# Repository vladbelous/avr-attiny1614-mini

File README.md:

# AVR Attiny1614 (tinyAVR 1-Series) mini board

This is a simple breakout board for Attiny1614 MCU with a button and some pins dedicated to switching loads via MOSFETs.

Attiny1614 ([datasheet](http://ww1.microchip.com/downloads/en/DeviceDoc/ATtiny1614-data-sheet-40001995A.pdf)) is a new 8-bit AVR part from tinyAVR 1-Series.
In many important ways its architecture is much closer to atxmega rather than to (previous) attiny/atmega parts.
In fact, in avr-gcc it is categorized under avrxmega3 architecture.

This particular board has:
* Pin PA4 connected to high-side P-MOSFET for powering/driving an external component, using same VIN supply and common GND. This pin is **active low**.
* Pin PA5  connected to low-side N-MOSFET for driving a load using a separate supply (VEXT pin). Grounds levels will be separate. This pin is **active high**.
* Footprints for optional pull-up resistors for I2C.

This board has already been fabricated and tested to work.
It is available as a [shared project on OSHPark](https://oshpark.com/shared_projects/I7XN0JuT).

### Note on UPDI/~RESET pin:
Pin PA0 (UPDI/~RESET) can be used for either programming (via UPDI protocol) or RESET source functionality, but *you have to choose* between the two via a fuse setting. By default the fuse is setup for UPDI.

If you set the fuses for RESET source, programming the chip will require applying 12V, which is somewhat inconvenient.

Some workarounds:
* Keep the fuse in UPDI mode: you can still use the pin as digital input, and hence implement reset functionality in software (e.g. via interrupt, polling, etc). This is less reliable, since it assumes your MCU is in working state.
* Use/create a bootloader (I'm not aware of any existing yet for this part) that will allow you to program the chip via UART (similar to Arduino). Then you can change the fuse to enable it as RESET source.

Overall, this presents some inconvenience in scenarios when you need a reliable RESET.
This may be important in low voltage situations -- if your MCU gets stuck in some non-working state, a physical RESET signal is needed. Some mitigation is paying more attention to BOD (brown-out detection) settings.

### Development toolchain:
See https://github.com/vladbelous/tinyAVR_gcc_setup for details on how to setup a toolchain based on avr-gcc, avrdude and jtag2updi.

## Schematic:

## Layout (front):

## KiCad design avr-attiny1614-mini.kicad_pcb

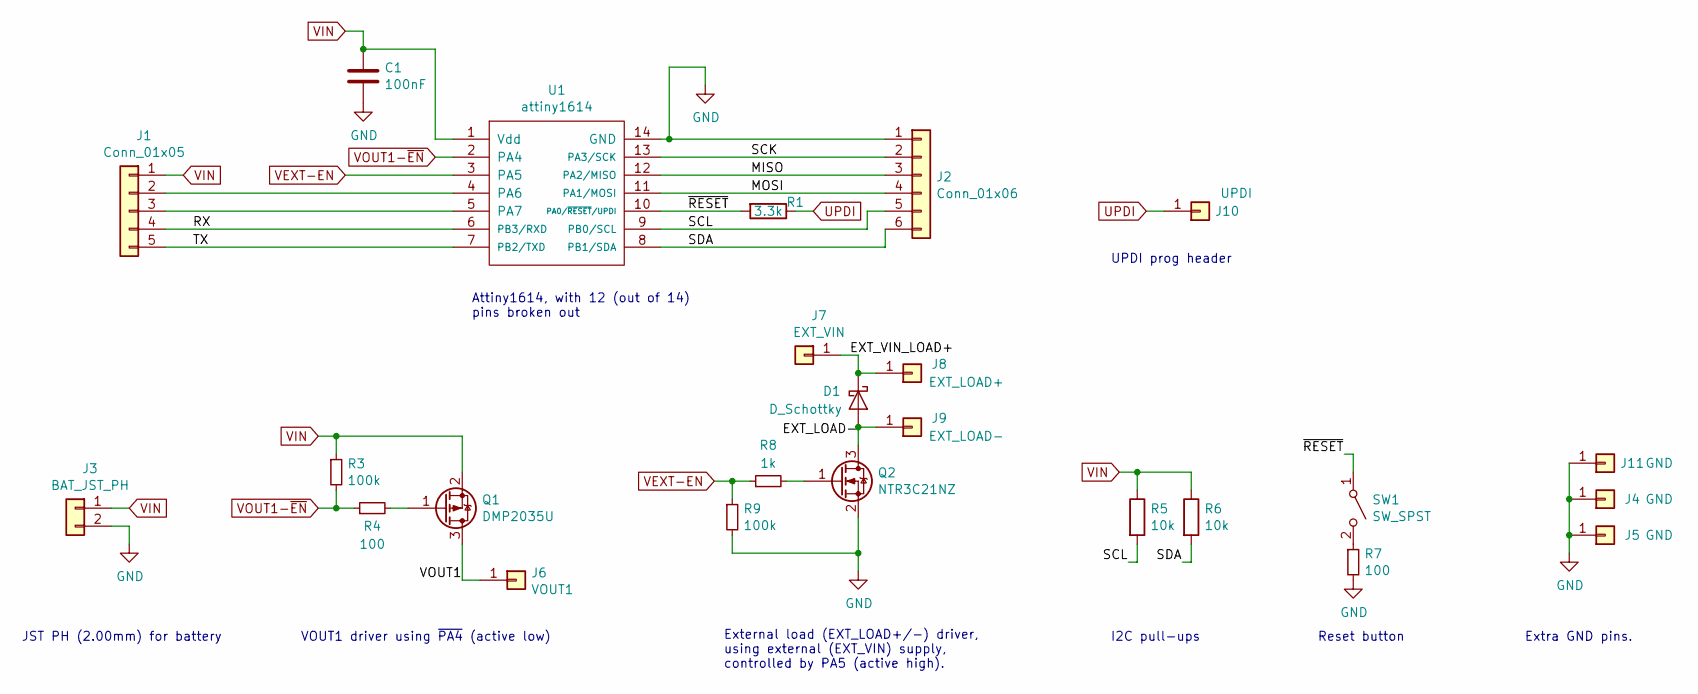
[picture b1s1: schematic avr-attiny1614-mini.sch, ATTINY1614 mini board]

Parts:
C1: 100nF; 0805_HS
D1: D_Schottky; 1206_Diode_HS
J1: Conn_01x05; Pin_Header_Straight_1x05_Pitch2.54mm
J2: Conn_01x06; Pin_Header_Straight_1x06_Pitch2.54mm
J3: BAT_JST_PH; JST_PH_S2B-PH-K_02x2.00mm_Angled
J4, J5, J11: GND; Pin_Header_Straight_1x01_Pitch2.54mm
J6: VOUT1; Pin_Header_Straight_1x01_Pitch2.54mm
J7: EXT_VIN; Pin_Header_Straight_1x01_Pitch2.54mm
J8: EXT_LOAD+; Pin_Header_Straight_1x01_Pitch2.54mm
J9: EXT_LOAD-; Pin_Header_Straight_1x01_Pitch2.54mm
J10: UPDI; Pin_Header_Straight_1x01_Pitch2.54mm
Q1: DMP2035U; SOT-23_HS
Q2: NTR3C21NZ; SOT-23_HS
R1: 3.3k; 0805_HS
R3, R9: 100k; 0805_HS
R4, R7: 100; 1206_HS
R5, R6: 10k; 0805_HS
R8: 1k; 0805_HS
SW1: SW_SPST; SW_PUSH_6mm
U1: attiny1614; SOIC-14_3.9x8.7mm_Pitch1.27mm_HS

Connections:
/EXT_LOAD-: D1.2 (A), J9.1, Q2.3 (D)
/EXT_VIN_LOAD+: D1.1 (K), J7.1, J8.1
/MISO: J2.3, U1.12 (PA2/MISO); also elsewhere on the board
/MOSI: J2.4, U1.11 (PA1/MOSI); also elsewhere on the board
/RX: J1.4, U1.6 (PB3/RXD); also elsewhere on the board
/SCK: J2.2, U1.13 (PA3/SCK); also elsewhere on the board
/SCL: J2.5, R5.2, U1.9 (PB0/SCL); also elsewhere on the board
/SDA: J2.6, R6.2, U1.8 (PB1/SDA); also elsewhere on the board
/TX: J1.5, U1.7 (PB2/TXD); also elsewhere on the board
/VOUT1: J6.1, Q1.3 (D)
/~RESET: R1.2, SW1.1 (A), U1.10 (PA0/~RESET~/UPDI); also elsewhere on the board
GND: C1.2, J2.1, J3.2, J4.1, J5.1, J11.1, Q2.2 (S), R7.2, R9.2, U1.14 (GND); also elsewhere on the board
unnamed 12: J1.2, U1.4 (PA6); also elsewhere on the board
unnamed 13: J1.3, U1.5 (PA7); also elsewhere on the board
unnamed: Q1.1 (G), R4.2
unnamed: Q2.1 (G), R8.2
unnamed: R7.1, SW1.2 (B)
UPDI: J10.1, R1.1
VEXT-EN: R8.1, R9.1, U1.3 (PA5); also elsewhere on the board
VIN: C1.1, J1.1, J3.1, Q1.2 (S), R3.1, R5.1, R6.1, U1.1 (Vdd); also elsewhere on the board
VOUT1-~EN: R3.2, R4.1, U1.2 (PA4); also elsewhere on the board

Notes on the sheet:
I2C pull-ups
Reset button
JST PH (2.00mm) for battery
VOUT1 driver using ~PA4~ (active low)
Attiny1614, with 12 (out of 14) pins broken out
External load (EXT_LOAD+/-) driver, using external (EXT_VIN) supply, controlled by PA5 (active high).
Extra GND pins.
UPDI prog header

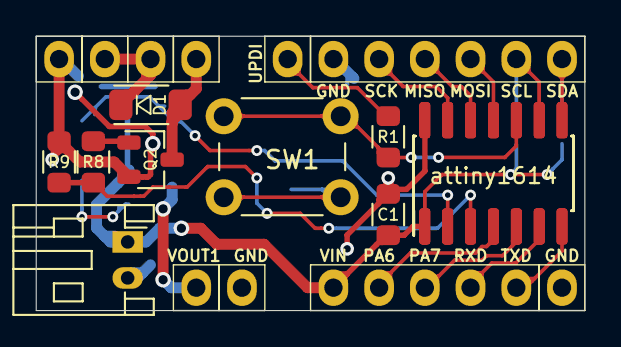
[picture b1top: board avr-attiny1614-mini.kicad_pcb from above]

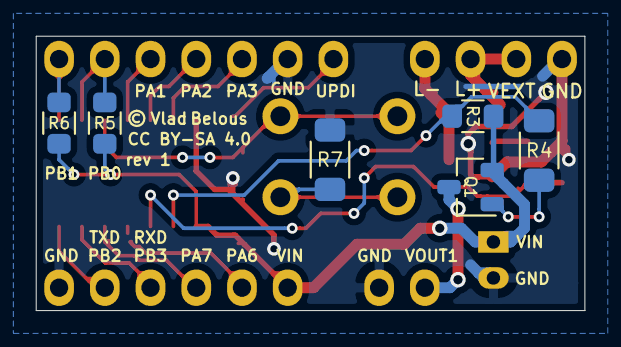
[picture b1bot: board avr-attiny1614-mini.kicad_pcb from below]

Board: 2 copper layers, 30.5 x 15.2 mm, 26 parts (6 on the bottom side), 21 nets.

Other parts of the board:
U1#2: attiny1614; SOIC-14_3.9x8.7mm_Pitch1.27mm_HS

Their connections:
/MISO: U1#2.12; also elsewhere on the board
/MOSI: U1#2.11; also elsewhere on the board
/RX: U1#2.6; also elsewhere on the board
/SCK: U1#2.13; also elsewhere on the board
/SCL: U1#2.9; also elsewhere on the board
/SDA: U1#2.8; also elsewhere on the board
/TX: U1#2.7; also elsewhere on the board
/~RESET: U1#2.10; also elsewhere on the board
GND: U1#2.14; also elsewhere on the board
unnamed 12: U1#2.4; also elsewhere on the board
unnamed 13: U1#2.5; also elsewhere on the board
VEXT-EN: U1#2.3; also elsewhere on the board
VIN: U1#2.1; also elsewhere on the board
VOUT1-~EN: U1#2.2; also elsewhere on the board

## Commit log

2018-12-09 Setup basic footprints
2018-12-09 Initial version of complete schematic
2018-12-10 Setup design rules
2018-12-10 Remove VSENSE. Add EXT_LOAD driver.
2018-12-10 Add micro USB for power
2018-12-10 Remove micro USB; minor tunings
2018-12-11 Layout exploring
2018-12-12 Approx placement for 1.2in x 0.6in board.
2018-12-12 Routing part 1
2018-12-12 Complete routing; Draft.
2018-12-13 Finished 1.2in x 0.6in layout
2018-12-13 License and readme
2018-12-14 Add images
2019-01-05 Add more description.

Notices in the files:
avr-attiny1614-mini.kicad_pcb:
License: CC BY-SA 4.0
CC BY-SA 4.0
avr-attiny1614-mini.sch:
creativecommons.org/licenses/by-sa/4.0
